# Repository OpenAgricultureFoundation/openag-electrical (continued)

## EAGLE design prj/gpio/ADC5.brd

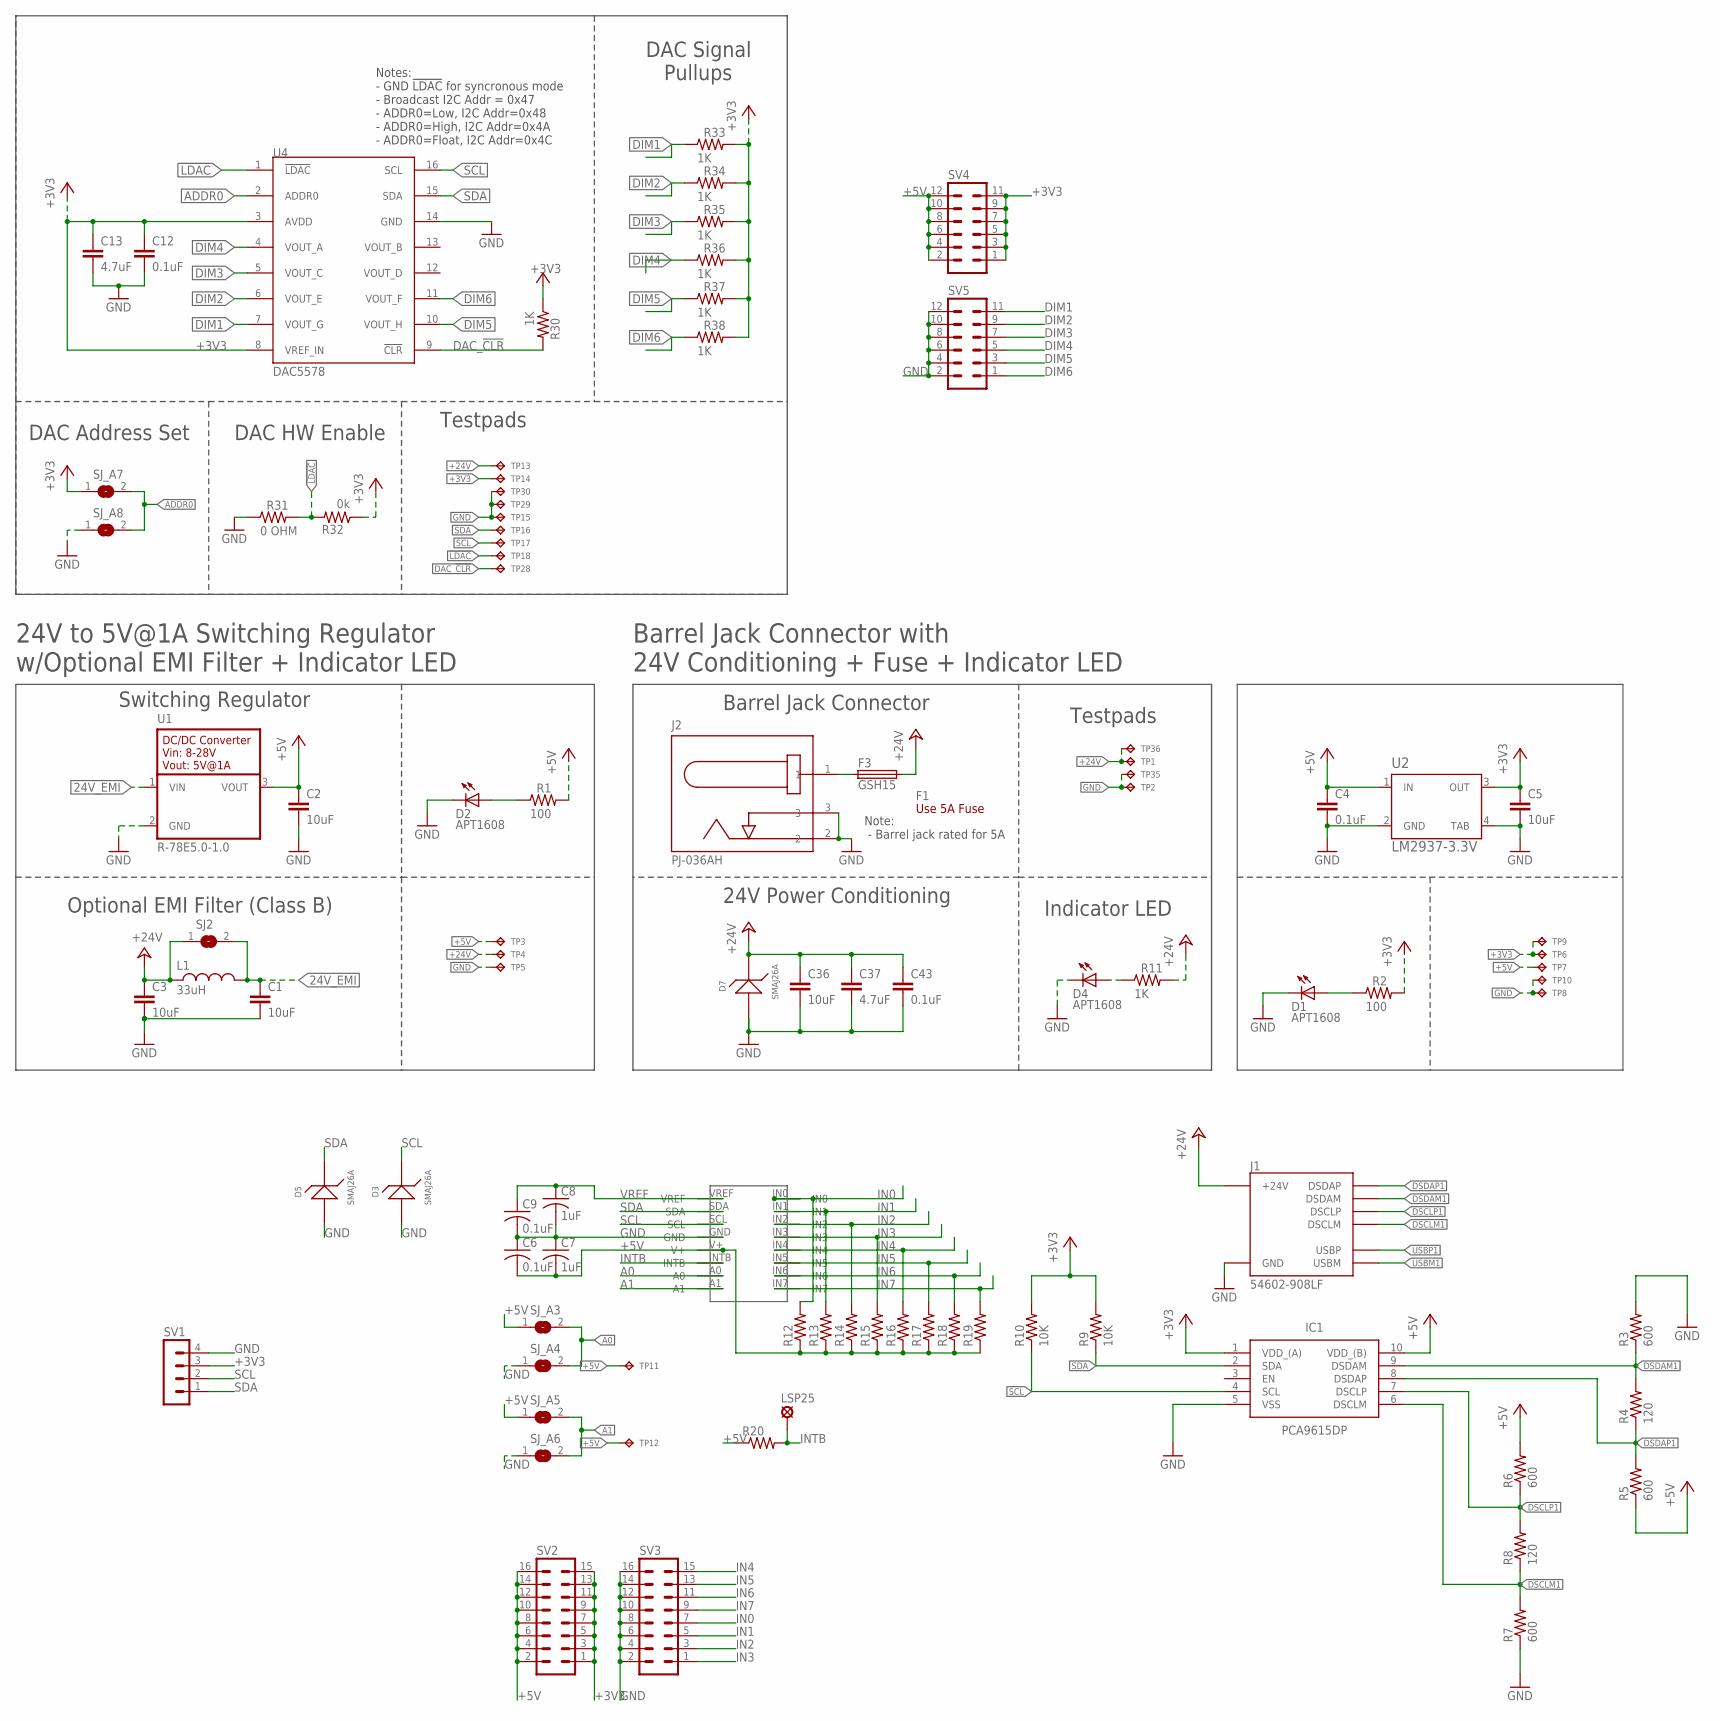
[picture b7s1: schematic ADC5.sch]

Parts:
C1, C2, C3, C5, C36: 10uF; C0805
C4, C6, C9, C12, C43: 0.1uF; C0603
C7, C8: 1uF; C0603
C13, C37: 4.7uF; C0805
D1, D2, D4: APT1608; CHIPLED_0603
D3, D5, D7: SMAJ26A; SMA
F1: Use 5A Fuse; FUSE-CARTRIDGE
F3: GSH15
IC1: PCA9615DP; SOP50P490X110-10N
J1: 54602-908LF; OPENAG-V1-RJ45
J2: PJ-036AH; BARREL-JACK-PJ-036AH
L1: 33uH; 29333C
LSP25: LSP10
R1, R2: 100; RC0603N
R3, R5, R6, R7: 600; R0603
R4, R8: 120; R0603
R9, R10: 10K; R0603
R11, R30, R33, R34, R35, R36, R37, R38: 1K; RC0603N
R12, R13, R14, R15, R16, R17, R18, R19, R20: R-US_R0603; R0603
R31: 0 OHM; RC0603N
R32: 0k; RC0603N
SJ2: EMI-BYPASS
SJ_A3, SJ_A4, SJ_A5, SJ_A6, SJ_A7, SJ_A8: SOLDERJUMPERREFLOW_NOPASTE; SJ1
SV1: MA04-1
SV2, SV3: MA08-2
SV4, SV5: MA06-2
TP1, TP2, TP6, TP7, TP8, TP9, TP10, TP11, TP12, TP13, TP14, TP15, TP16, TP17, TP18, TP28, TP29, TP30, TP35, TP36: TPTP04R; TP04R
TP3, TP4, TP5: TPTP06R; TP06R
U1: R-78E5.0-1.0
U2: LM2937-3.3V; MP04A
U4: DAC5578; TSSOP16
U$1: ADC128D818; TSSOP16

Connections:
24V_EMI: C1.1, L1.2, SJ2.2, U1.1 (VIN)
24V_IN: F3.1, J2.1
!LDAC!: R31.2, R32.2, TP18.1, U4.1 (!LDAC!)
+3V3: C5.1, C12.1, C13.1, IC1.1 (VDD_(A)), R2.2, R9.2, R10.2, R30.1, R32.1, R33.2, R34.2, R35.2, R36.2, R37.2, R38.2, SJ_A7.1, SV1.3, SV2.1, SV2.3, SV2.5, SV2.7, SV2.9, SV2.11, SV2.13, SV2.15, SV4.1, SV4.3, SV4.5, SV4.7, SV4.9, SV4.11, TP6.1, TP9.1, TP14.1, U2.3 (OUT), U4.3 (AVDD), U4.8 (VREF_IN)
+5V: C2.1, C4.1, C6.2, C7.2, IC1.10 (VDD_(B)), R1.2, R5.1, R6.2, R12.1, R13.1, R14.1, R15.1, R16.1, R17.1, R18.1, R19.1, R20.1, SJ_A3.1, SJ_A5.1, SV2.2, SV2.4, SV2.6, SV2.8, SV2.10, SV2.12, SV2.14, SV2.16, SV4.2, SV4.4, SV4.6, SV4.8, SV4.10, SV4.12, TP3.TP, TP7.1, TP11.1, TP12.1, U1.3 (VOUT), U2.1 (IN), U$1.V+
+24V: C3.1, C36.1, C37.1, C43.1, D7.1, F3.2, J1.24V(6) (+24V), L1.1, R11.2, SJ2.1, TP1.1, TP4.TP, TP13.1, TP36.1
A0: SJ_A3.2, SJ_A4.2, U$1.A0
A1: SJ_A5.2, SJ_A6.2, U$1.A1
ADDR0: SJ_A7.2, SJ_A8.2, U4.2 (ADDR0)
DAC_!CLR!: R30.2, TP28.1, U4.9 (!CLR!)
DIM1: R33.1, SV5.11, U4.7 (VOUT_G)
DIM2: R34.1, SV5.9, U4.6 (VOUT_E)
DIM3: R35.1, SV5.7, U4.5 (VOUT_C)
DIM4: R36.1, SV5.5, U4.4 (VOUT_A)
DIM5: R37.1, SV5.3, U4.10 (VOUT_H)
DIM6: R38.1, SV5.1, U4.11 (VOUT_F)
DSCLM1: IC1.6 (DSCLM), J1.DSCLM(5) (DSCLM), R7.2, R8.1
DSCLP1: IC1.7 (DSCLP), J1.DSCLP(4) (DSCLP), R6.1, R8.2
DSDAM1: IC1.9 (DSDAM), J1.DSDAM(2) (DSDAM), R3.1, R4.2
DSDAP1: IC1.8 (DSDAP), J1.DSDAP(1) (DSDAP), R4.1, R5.2
GND: C1.2, C2.2, C3.2, C4.2, C5.2, C6.1, C7.1, C8.2, C9.2, C12.2, C13.2, C36.2, C37.2, C43.2, D1.C, D2.C, D3.2, D4.C, D5.2, D7.2, IC1.5 (VSS), J1.GND(3) (GND), J2.2, J2.3, R3.2, R7.1, R31.1, SJ_A4.1, SJ_A6.1, SJ_A8.1, SV1.4, SV3.2, SV3.4, SV3.6, SV3.8, SV3.10, SV3.12, SV3.14, SV3.16, SV5.2, SV5.4, SV5.6, SV5.8, SV5.10, SV5.12, TP2.1, TP5.TP, TP8.1, TP10.1, TP15.1, TP29.1, TP30.1, TP35.1, U1.2 (GND), U2.2 (GND), U2.4 (TAB), U4.14 (GND), U$1.GND
IN0: R12.2, SV3.7, U$1.IN0
IN1: R13.2, SV3.5, U$1.IN1
IN2: R14.2, SV3.3, U$1.IN2
IN3: R15.2, SV3.1, U$1.IN3
IN4: R16.2, SV3.15, U$1.IN4
IN5: R17.2, SV3.13, U$1.IN5
IN6: R18.2, SV3.11, U$1.IN6
IN7: R19.2, SV3.9, U$1.IN7
INTB: LSP25.MP, R20.2, U$1.INTB
unnamed: D1.A, R2.1
unnamed: D2.A, R1.1
unnamed: D4.A, R11.1
SCL: D3.1, IC1.4 (SCL), R10.1, SV1.2, TP17.1, U4.16 (SCL), U$1.SCL
SDA: D5.1, IC1.2 (SDA), R9.1, SV1.1, TP16.1, U4.15 (SDA), U$1.SDA
USBM1: J1.USBM(8) (USBM)
USBP1: J1.USBP(7) (USBP)
VREF: C8.1, C9.1, U$1.VREF

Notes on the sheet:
Barrel Jack Connector
Barrel Jack Connector with 24V Conditioning + Fuse + Indicator LED
24V Power Conditioning
Indicator LED
Testpads
Note: - Barrel jack rated for 5A
24V to 5V@1A Switching Regulator w/Optional EMI Filter + Indicator LED
Switching Regulator
Optional EMI Filter (Class B)
Notes: - GND !LDAC! for syncronous mode - Broadcast I2C Addr = 0x47 - ADDR0=Low, I2C Addr=0x48 - ADDR0=High, I2C Addr=0x4A - ADDR0=Float, I2C Addr=0x4C
DAC Signal Pullups
DAC Address Set
DAC HW Enable

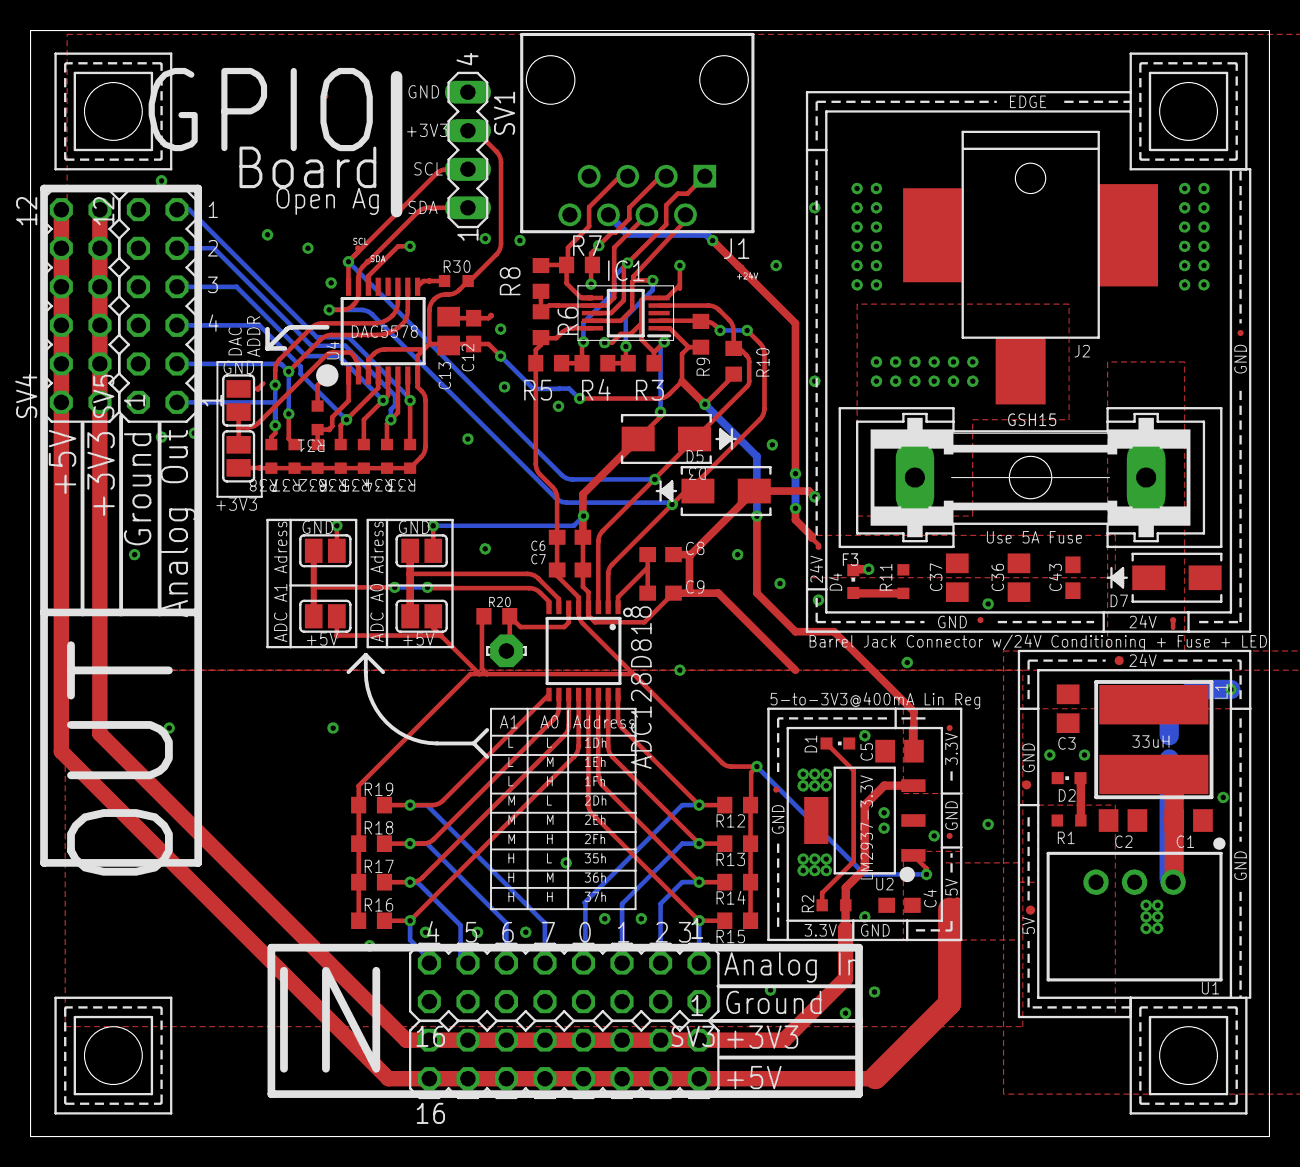
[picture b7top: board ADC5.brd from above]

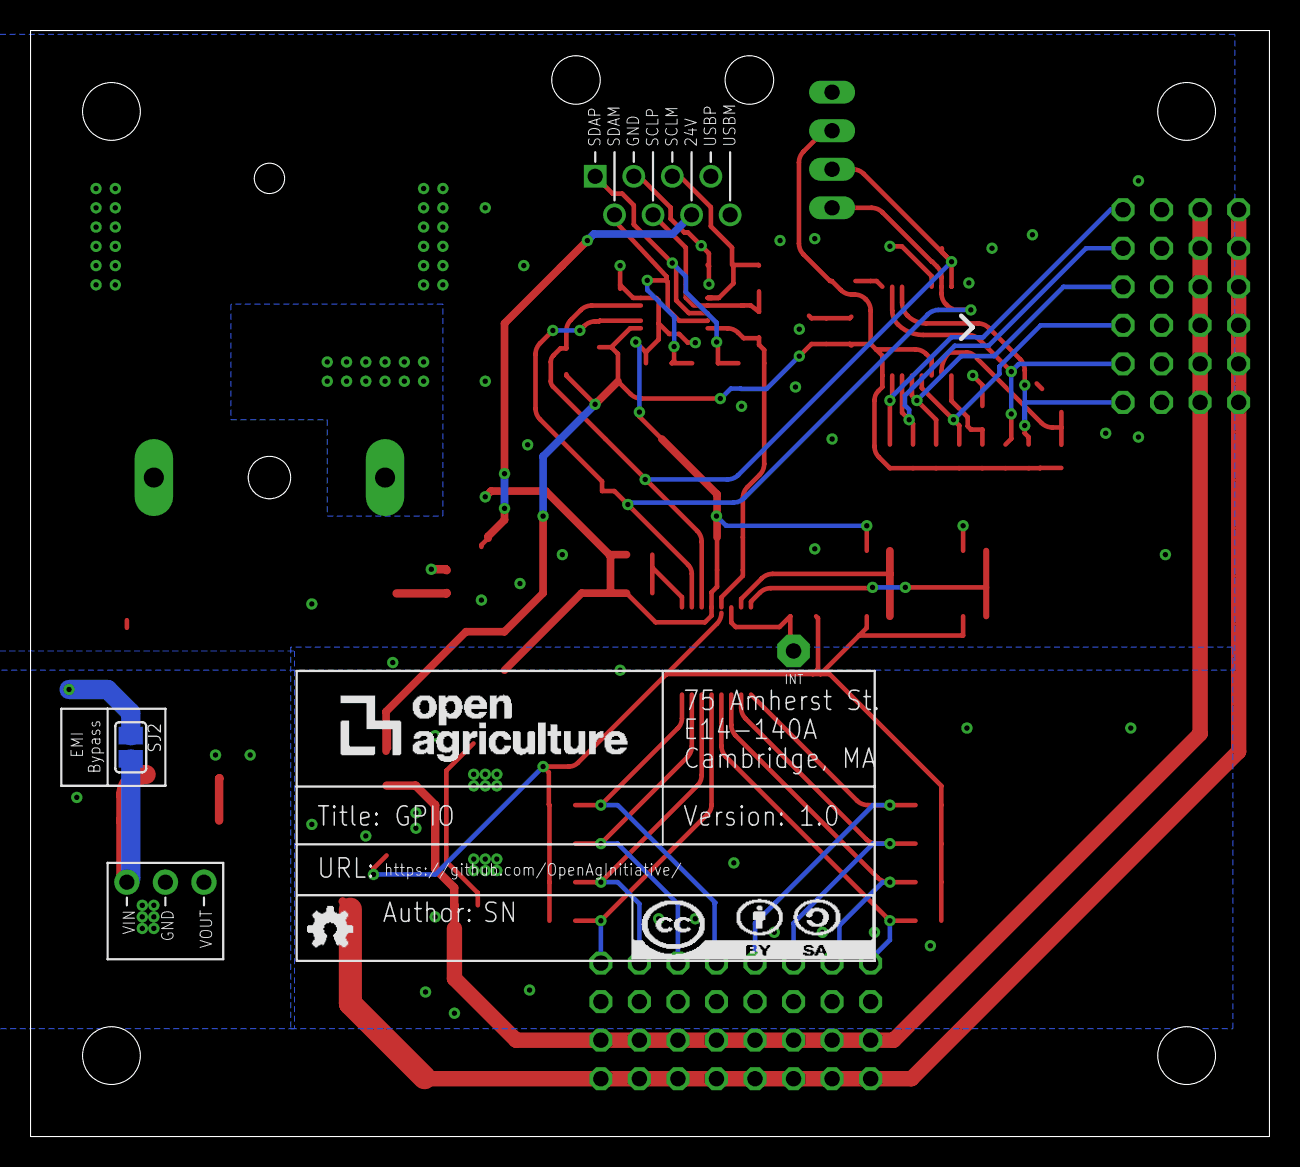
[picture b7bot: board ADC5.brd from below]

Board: 2 copper layers, 81.7 x 72.9 mm, 100 parts (2 on the bottom side), 36 nets.

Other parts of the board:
ATTRIBUTES: DOCFIELD
U$2, U$3, U$4, U$5: CORNER

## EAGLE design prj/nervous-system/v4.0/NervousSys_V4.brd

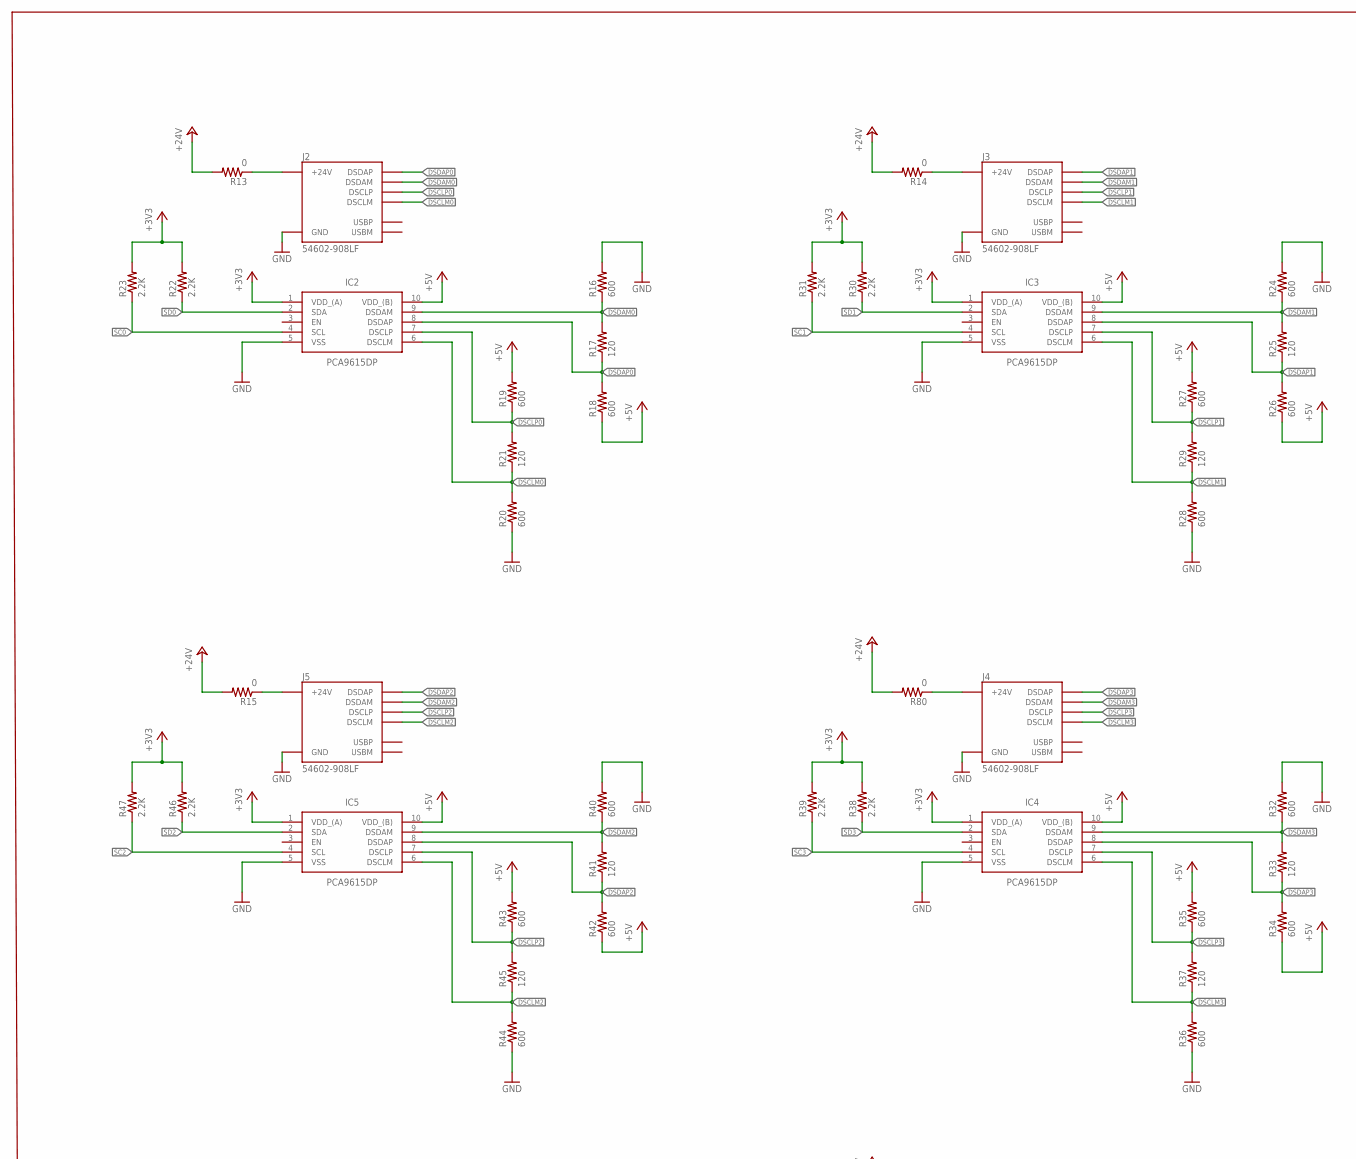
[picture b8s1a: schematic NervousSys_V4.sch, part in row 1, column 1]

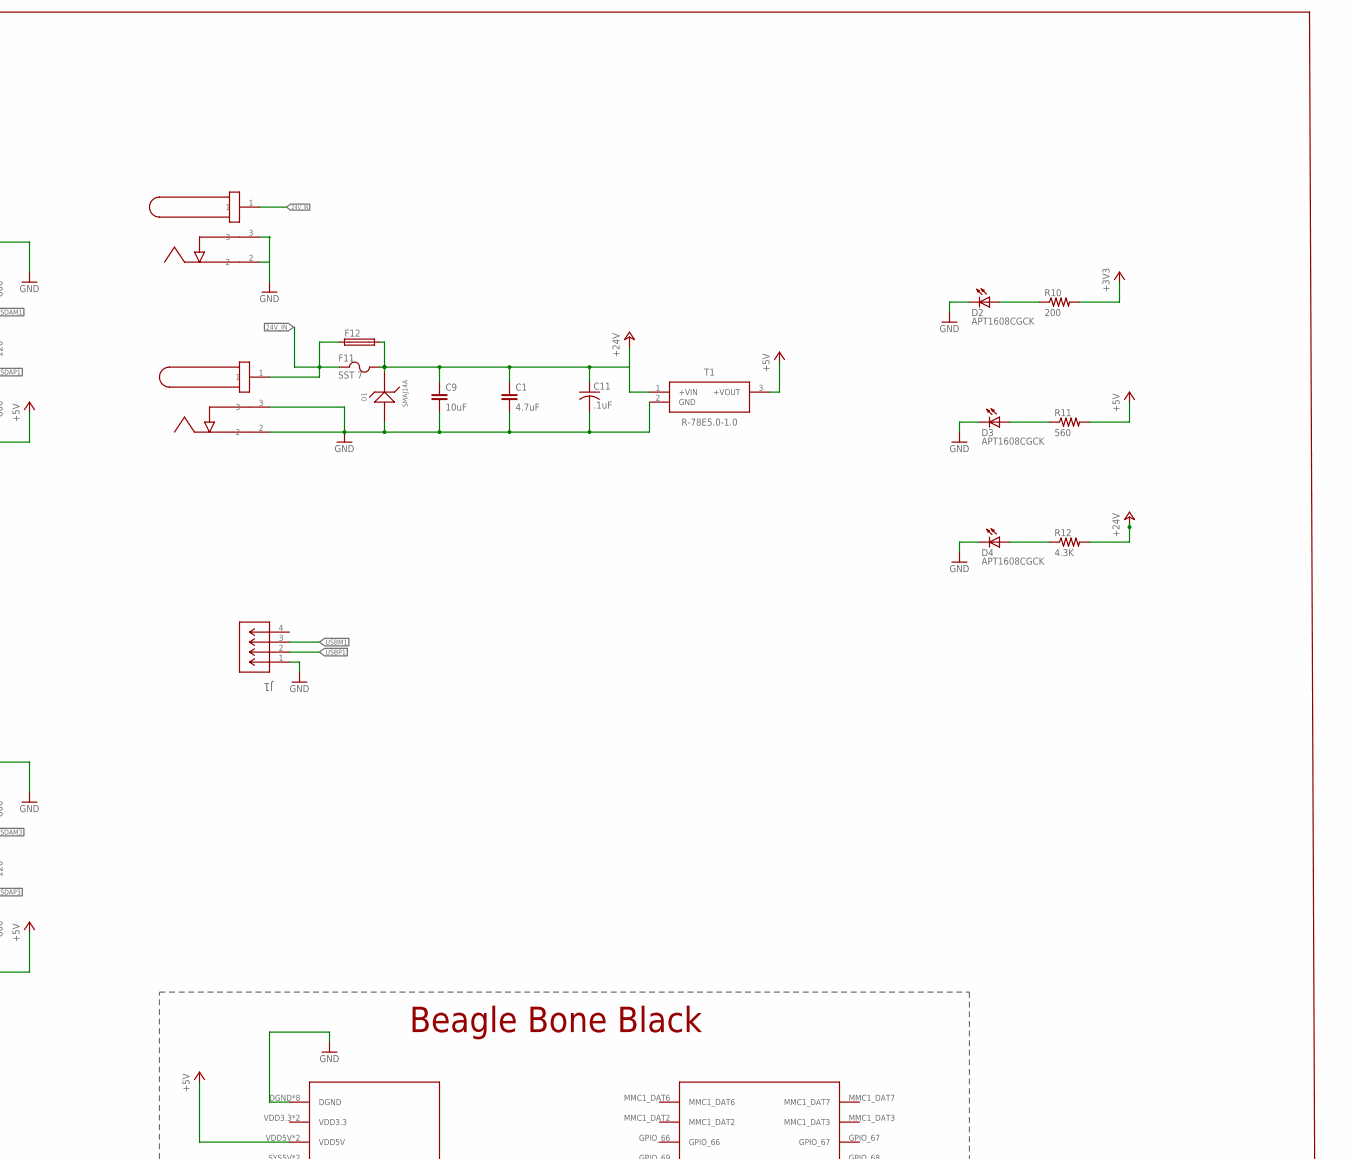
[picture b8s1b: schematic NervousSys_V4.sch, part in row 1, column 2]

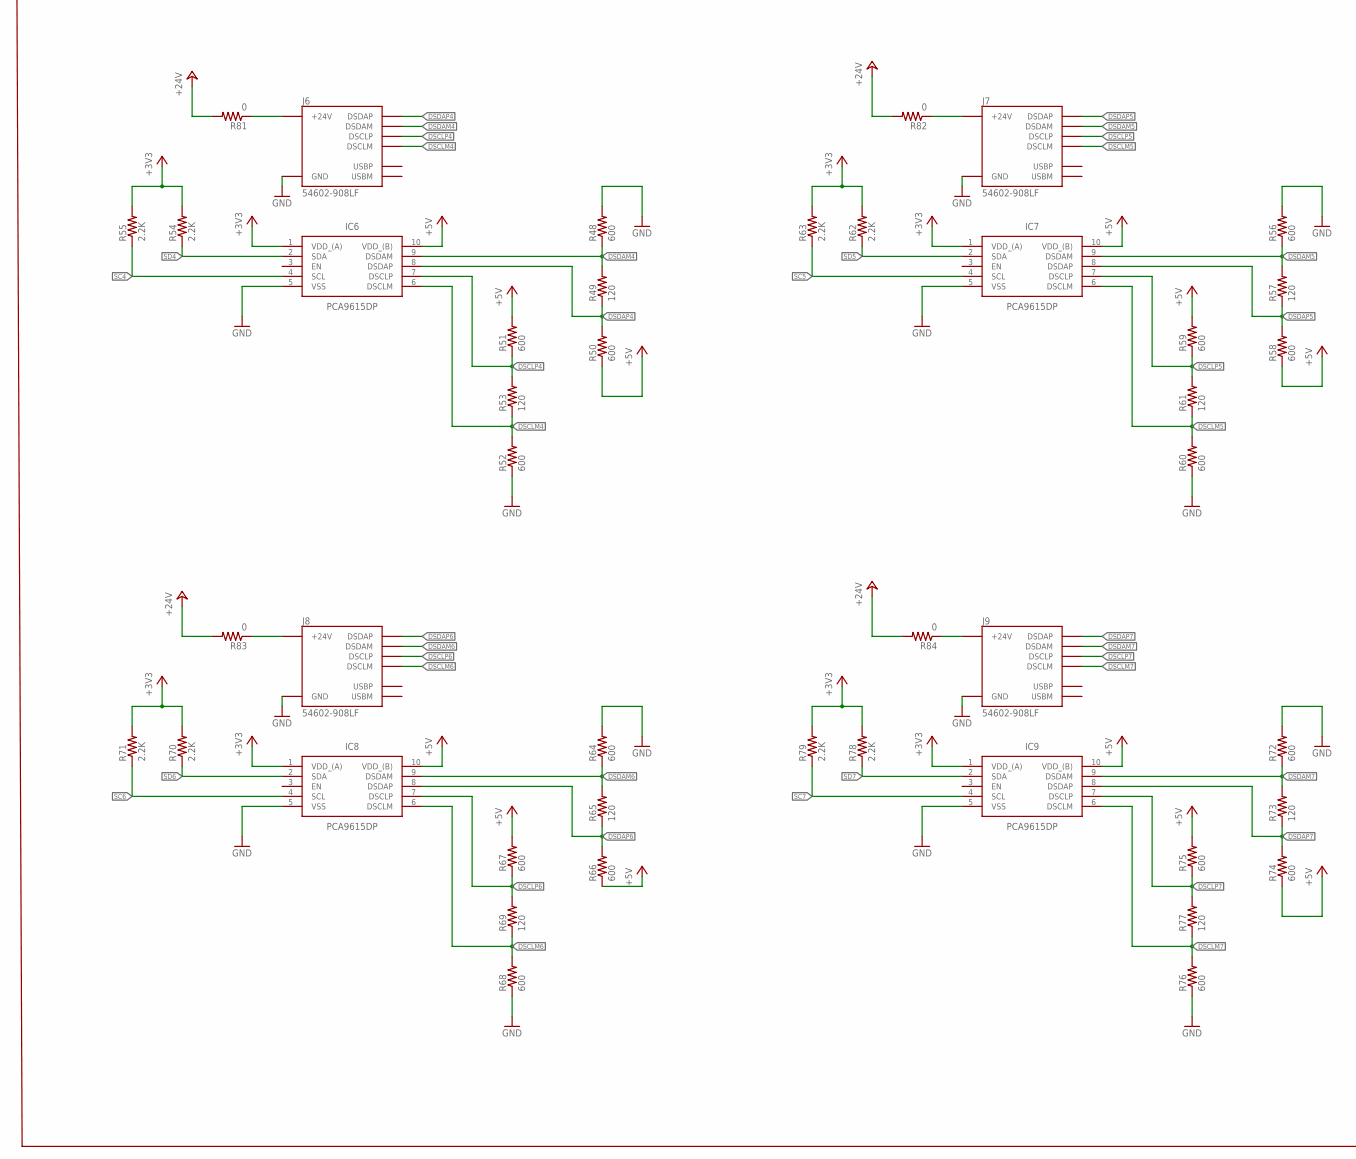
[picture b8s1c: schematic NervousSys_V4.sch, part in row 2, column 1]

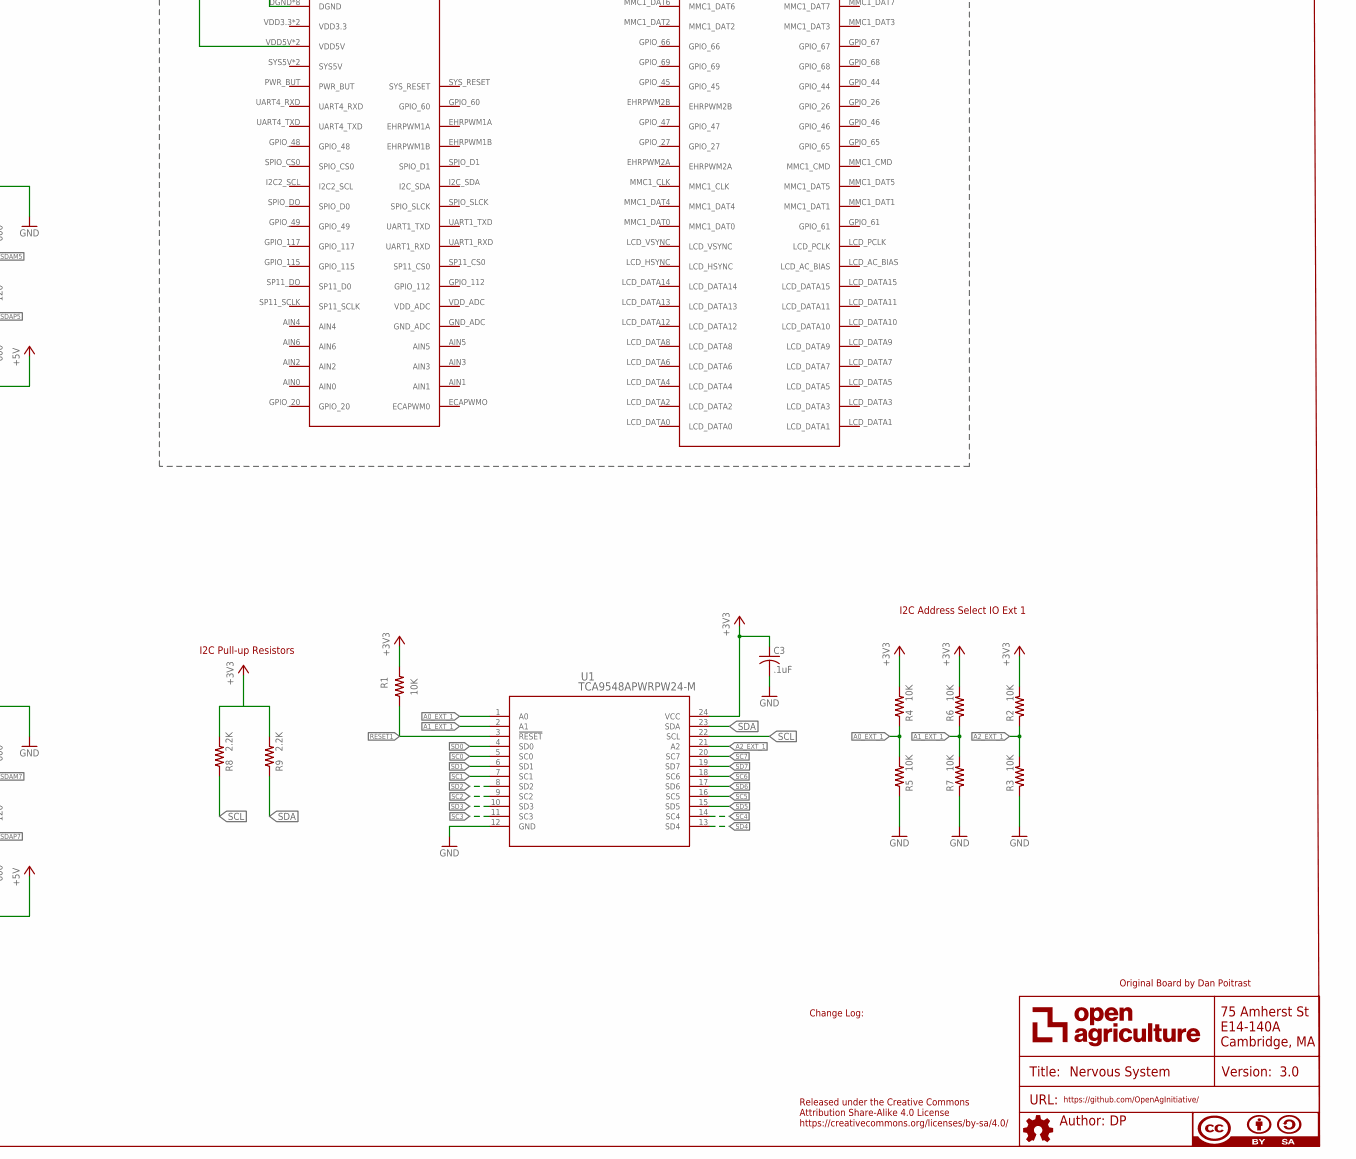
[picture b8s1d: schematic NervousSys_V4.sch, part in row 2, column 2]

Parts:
ATTRIBUTES: DOCFIELD
C1: 4.7uF; CAP_C1206
C3, C11: .1uF; C0603@1
C9: 10uF; C1206
D1: SMAJ14A; DO-214AC
D2, D3, D4: APT1608CGCK; CHIPLED_0603
F11: SST 7; SS
F12: GSH15
IC2, IC3, IC4, IC5, IC6, IC7, IC8, IC9: PCA9615DP; SOP50P490X110-10N
J1: 87583-2010BLF; CONN_USB-87583
J2, J3, J4, J5, J6, J7, J8, J9: 54602-908LF; OPENAG-V1-RJ45
R1: 10K; R0603
R2, R3, R4, R5, R6, R7: 10K; 0603-RES
R8, R9: 2.2K; 0603-RES
R10: 200; RC0603N
R11: 560; RC0603N
R12: 4.3K; RC0603N
R13, R14, R15, R80, R81, R82, R83, R84: 0; R0603
R16, R18, R19, R20, R24, R26, R27, R28, R32, R34, R35, R36, R40, R42, R43, R44, R48, R50, R51, R52, R56, R58, R59, R60, R64, R66, R67, R68, R72, R74, R75, R76: 600; R0603
R17, R21, R25, R29, R33, R37, R41, R45, R49, R53, R57, R61, R65, R69, R73, R77: 120; R0603
R22, R23, R30, R31, R38, R39, R46, R47, R54, R55, R62, R63, R70, R71, R78, R79: 2.2K; R0603
T1: R-78E5.0-1.0
U1: TCA9548APWRPW24-M; PW24-M
U$1, U$3: PJ-036AH
U$4: BBB_SMD; 23PINHEADERSMD

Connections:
24V_IN: F11.1, F12.1, U$1.1, U$3.1
+3V3: C3.1, IC2.1 (VDD_(A)), IC3.1 (VDD_(A)), IC4.1 (VDD_(A)), IC5.1 (VDD_(A)), IC6.1 (VDD_(A)), IC7.1 (VDD_(A)), IC8.1 (VDD_(A)), IC9.1 (VDD_(A)), R1.2, R2.2, R4.2, R6.2, R8.2, R9.2, R10.2, R22.2, R23.2, R30.2, R31.2, R38.2, R39.2, R46.2, R47.2, R54.2, R55.2, R62.2, R63.2, R70.2, R71.2, R78.2, R79.2, U1.24 (VCC)
+5V: IC2.10 (VDD_(B)), IC3.10 (VDD_(B)), IC4.10 (VDD_(B)), IC5.10 (VDD_(B)), IC6.10 (VDD_(B)), IC7.10 (VDD_(B)), IC8.10 (VDD_(B)), IC9.10 (VDD_(B)), R11.2, R18.1, R19.2, R26.1, R27.2, R34.1, R35.2, R42.1, R43.2, R50.1, R51.2, R58.1, R59.2, R66.1, R67.2, R74.1, R75.2, T1.3 (+VOUT), U$4.VDD5V, U$4.VDD5V1 (VDD5V)
+24V: C1.1, C9.1, C11.1, D1.C, F11.2, F12.2, R12.2, R13.2, R14.2, R15.2, R80.2, R81.2, R82.2, R83.2, R84.2, T1.1 (+VIN)
A0_EXT_1: R4.1, R5.2, U1.1 (A0)
A1_EXT_1: R6.1, R7.2, U1.2 (A1)
A2_EXT_1: R2.1, R3.2, U1.21 (A2)
DSCLM0: IC2.6 (DSCLM), J2.DSCLM(5) (DSCLM), R20.2, R21.1
DSCLM1: IC3.6 (DSCLM), J3.DSCLM(5) (DSCLM), R28.2, R29.1
DSCLM2: IC5.6 (DSCLM), J5.DSCLM(5) (DSCLM), R44.2, R45.1
DSCLM3: IC4.6 (DSCLM), J4.DSCLM(5) (DSCLM), R36.2, R37.1
DSCLM4: IC6.6 (DSCLM), J6.DSCLM(5) (DSCLM), R52.2, R53.1
DSCLM5: IC7.6 (DSCLM), J7.DSCLM(5) (DSCLM), R60.2, R61.1
DSCLM6: IC8.6 (DSCLM), J8.DSCLM(5) (DSCLM), R68.2, R69.1
DSCLM7: IC9.6 (DSCLM), J9.DSCLM(5) (DSCLM), R76.2, R77.1
DSCLP0: IC2.7 (DSCLP), J2.DSCLP(4) (DSCLP), R19.1, R21.2
DSCLP1: IC3.7 (DSCLP), J3.DSCLP(4) (DSCLP), R27.1, R29.2
DSCLP2: IC5.7 (DSCLP), J5.DSCLP(4) (DSCLP), R43.1, R45.2
DSCLP3: IC4.7 (DSCLP), J4.DSCLP(4) (DSCLP), R35.1, R37.2
DSCLP4: IC6.7 (DSCLP), J6.DSCLP(4) (DSCLP), R51.1, R53.2
DSCLP5: IC7.7 (DSCLP), J7.DSCLP(4) (DSCLP), R59.1, R61.2
DSCLP6: IC8.7 (DSCLP), J8.DSCLP(4) (DSCLP), R67.1, R69.2
DSCLP7: IC9.7 (DSCLP), J9.DSCLP(4) (DSCLP), R75.1, R77.2
DSDAM0: IC2.9 (DSDAM), J2.DSDAM(2) (DSDAM), R16.1, R17.2
DSDAM1: IC3.9 (DSDAM), J3.DSDAM(2) (DSDAM), R24.1, R25.2
DSDAM2: IC5.9 (DSDAM), J5.DSDAM(2) (DSDAM), R40.1, R41.2
DSDAM3: IC4.9 (DSDAM), J4.DSDAM(2) (DSDAM), R32.1, R33.2
DSDAM4: IC6.9 (DSDAM), J6.DSDAM(2) (DSDAM), R48.1, R49.2
DSDAM5: IC7.9 (DSDAM), J7.DSDAM(2) (DSDAM), R56.1, R57.2
DSDAM6: IC8.9 (DSDAM), J8.DSDAM(2) (DSDAM), R64.1, R65.2
DSDAM7: IC9.9 (DSDAM), J9.DSDAM(2) (DSDAM), R72.1, R73.2
DSDAP0: IC2.8 (DSDAP), J2.DSDAP(1) (DSDAP), R17.1, R18.2
DSDAP1: IC3.8 (DSDAP), J3.DSDAP(1) (DSDAP), R25.1, R26.2
DSDAP2: IC5.8 (DSDAP), J5.DSDAP(1) (DSDAP), R41.1, R42.2
DSDAP3: IC4.8 (DSDAP), J4.DSDAP(1) (DSDAP), R33.1, R34.2
DSDAP4: IC6.8 (DSDAP), J6.DSDAP(1) (DSDAP), R49.1, R50.2
DSDAP5: IC7.8 (DSDAP), J7.DSDAP(1) (DSDAP), R57.1, R58.2
DSDAP6: IC8.8 (DSDAP), J8.DSDAP(1) (DSDAP), R65.1, R66.2
DSDAP7: IC9.8 (DSDAP), J9.DSDAP(1) (DSDAP), R73.1, R74.2
GND: C1.2, C3.2, C9.2, C11.2, D1.A, D2.C, D3.C, D4.C, IC2.5 (VSS), IC3.5 (VSS), IC4.5 (VSS), IC5.5 (VSS), IC6.5 (VSS), IC7.5 (VSS), IC8.5 (VSS), IC9.5 (VSS), J1.1, J2.GND(3) (GND), J3.GND(3) (GND), J4.GND(3) (GND), J5.GND(3) (GND), J6.GND(3) (GND), J7.GND(3) (GND), J8.GND(3) (GND), J9.GND(3) (GND), R3.1, R5.1, R7.1, R16.2, R20.1, R24.2, R28.1, R32.2, R36.1, R40.2, R44.1, R48.2, R52.1, R56.2, R60.1, R64.2, R68.1, R72.2, R76.1, T1.2 (GND), U1.12 (GND), U$1.2, U$1.3, U$3.2, U$3.3, U$4.DGND, U$4.DGND1 (DGND), U$4.DGND2 (DGND), U$4.DGND3 (DGND), U$4.DGND4 (DGND), U$4.DGND5 (DGND), U$4.DGND6 (DGND), U$4.DGND7 (DGND)
unnamed: J2.24V(6) (+24V), R13.1
unnamed: D3.A, R11.1
unnamed: J3.24V(6) (+24V), R14.1
unnamed: D4.A, R12.1
unnamed: J5.24V(6) (+24V), R15.1
unnamed: J4.24V(6) (+24V), R80.1
unnamed: J6.24V(6) (+24V), R81.1
unnamed: J7.24V(6) (+24V), R82.1
unnamed: J8.24V(6) (+24V), R83.1
unnamed: J9.24V(6) (+24V), R84.1
unnamed: D2.A, R10.1
RESET1: R1.1, U1.3 (!RESET)
SC0: IC2.4 (SCL), R23.1, U1.5 (SC0)
SC1: IC3.4 (SCL), R31.1, U1.7 (SC1)
SC2: IC5.4 (SCL), R47.1, U1.9 (SC2)
SC3: IC4.4 (SCL), R39.1, U1.11 (SC3)
SC4: IC6.4 (SCL), R55.1, U1.14 (SC4)
SC5: IC7.4 (SCL), R63.1, U1.16 (SC5)
SC6: IC8.4 (SCL), R71.1, U1.18 (SC6)
SC7: IC9.4 (SCL), R79.1, U1.20 (SC7)
SCL: R8.1, U1.22 (SCL)
SD0: IC2.2 (SDA), R22.1, U1.4 (SD0)
SD1: IC3.2 (SDA), R30.1, U1.6 (SD1)
SD2: IC5.2 (SDA), R46.1, U1.8 (SD2)
SD3: IC4.2 (SDA), R38.1, U1.10 (SD3)
SD4: IC6.2 (SDA), R54.1, U1.13 (SD4)
SD5: IC7.2 (SDA), R62.1, U1.15 (SD5)
SD6: IC8.2 (SDA), R70.1, U1.17 (SD6)
SD7: IC9.2 (SDA), R78.1, U1.19 (SD7)
SDA: R9.1, U1.23 (SDA)
USBM1: J1.3
USBP1: J1.2

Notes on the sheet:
Original Board by Dan Poitrast
Change Log:
I2C Pull-up Resistors
Released under the Creative Commons Attribution Share-Alike 4.0 License https://creativecommons.org/licenses/by-sa/4.0/
I2C Address Select IO Ext 1
